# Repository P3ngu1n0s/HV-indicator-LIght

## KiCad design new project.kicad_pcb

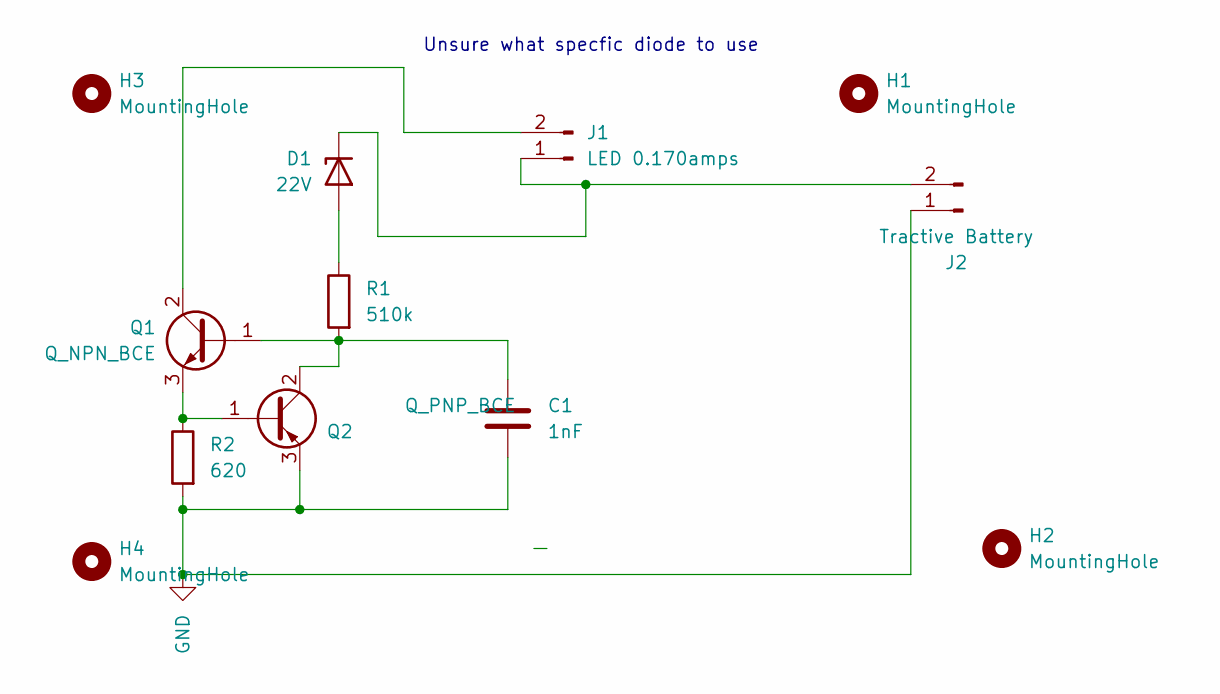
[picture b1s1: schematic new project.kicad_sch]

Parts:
C1: 1nF; C_0603_1608Metric
D1: 22V; D_DO-41_SOD81_P10.16mm_Horizontal
H1, H2, H3, H4: MountingHole; MountingHole_2.1mm
J1: LED 0.170amps; Molex_Micro-Fit_3.0_43650-0200_1x02_P3.00mm_Horizontal
J2: Tractive Battery; Molex_Micro-Fit_3.0_43650-0200_1x02_P3.00mm_Horizontal
Q1: Q_NPN_BCE; SOT-223-3_TabPin2
Q2: Q_PNP_BCE; SOT-223-3_TabPin2
R1: 510k; R_Axial_DIN0207_L6.3mm_D2.5mm_P10.16mm_Horizontal
R2: 620; R_Axial_DIN0207_L6.3mm_D2.5mm_P10.16mm_Horizontal

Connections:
GND: C1.2, J2.1, Q2.3 (E), R2.2
unnamed: D1.2 (A), R1.1
unnamed: D1.1 (K), J1.1, J2.2
unnamed: J1.2, Q1.2 (C)
unnamed: C1.1, Q1.1 (B), Q2.2 (C), R1.2
unnamed: Q1.3 (E), Q2.1 (B), R2.1

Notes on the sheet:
Unsure what specfic diode to use

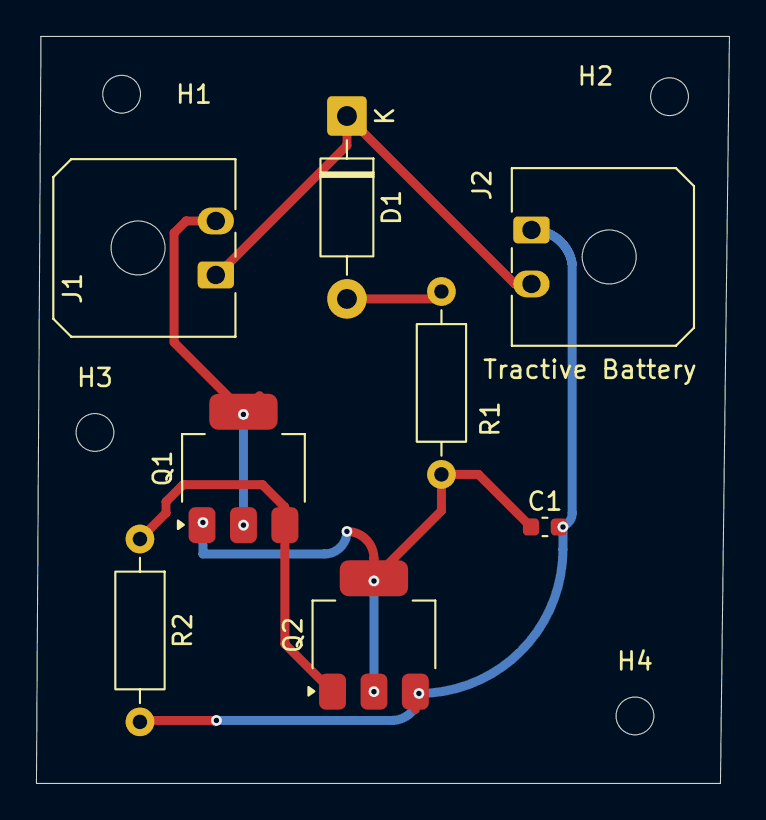
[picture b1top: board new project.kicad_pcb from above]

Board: 2 copper layers, 38.5 x 41.5 mm, 12 parts (0 on the bottom side), 6 nets.

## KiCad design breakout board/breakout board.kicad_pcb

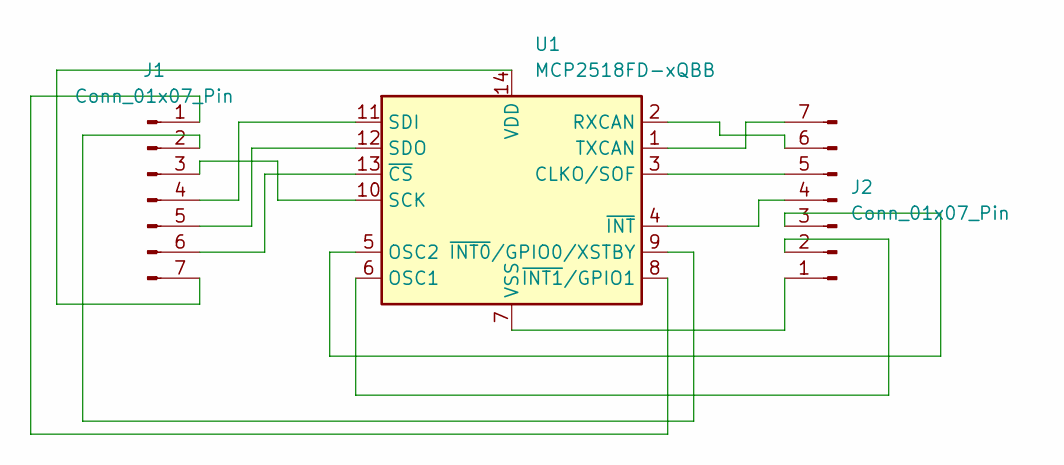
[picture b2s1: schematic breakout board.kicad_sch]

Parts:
J1, J2: Conn_01x07_Pin; PinHeader_1x07_P2.54mm_Vertical
U1: MCP2518FD-xQBB; DFN-14-1EP_3x4.5mm_P0.65mm_EP1.65x4.25mm

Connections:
unnamed: J1.1, U1.8 (~INT1/GPIO1)
unnamed: J1.2, U1.9 (~INT0/GPIO0/XSTBY)
unnamed: J1.3, U1.10 (SCK)
unnamed: J1.4, U1.11 (SDI)
unnamed: J1.5, U1.12 (SDO)
unnamed: J1.6, U1.13 (~CS)
unnamed: J1.7, U1.14 (VDD)
unnamed: J2.1, U1.7 (VSS), U1.15 (VSS)
unnamed: J2.2, U1.6 (OSC1)
unnamed: J2.3, U1.5 (OSC2)
unnamed: J2.4, U1.4 (~INT)
unnamed: J2.5, U1.3 (CLKO/SOF)
unnamed: J2.6, U1.2 (RXCAN)
unnamed: J2.7, U1.1 (TXCAN)

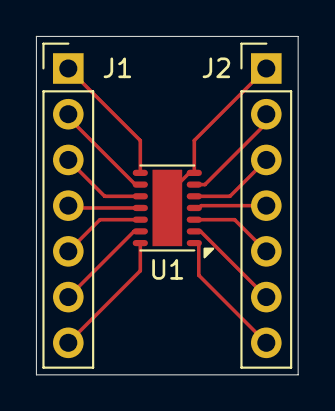
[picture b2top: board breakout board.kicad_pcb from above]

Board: 2 copper layers, 14.5 x 18.8 mm, 3 parts (0 on the bottom side), 14 nets.

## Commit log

2025-09-12 This is HV Inidcator for E25
2025-09-23 fixed
    fix
2025-09-23 sure
2025-09-23 Change
    NEW HV_INDICATOR folder
2025-09-23 something
2025-09-23 footprints added
2025-09-23 all footprints added and they ready for wriing
2025-09-23 Changed Resistor and LED footprint
2025-09-23 Wiring Done
2025-09-23 Autosave
2025-09-24 add everything
2025-09-24 everything works type
2025-09-24 Check
    Check
2025-09-25 Changed 1800 to 18000
    Resistor Value
2025-09-25 Updated HV
    Changed Resistor, Wiring and more.
2025-09-25 Push
2025-09-25 sure lets hope this fixes it
2025-09-26 UPDATE
    This should update everything now?? THINGS KEEP GETTING DELETED
2025-09-26 Update
    NOT LOADING IN GITHUB?
2025-09-26 Prototype
    Some error stills, but structure is overall built
2025-09-26 work
2025-09-26 Finally fixed
    Please upload the changes
2025-09-26 Check
    Redoing Wiring
2025-09-26 FInished
    Done
2025-09-26 Test
    Test
2025-09-26 Is it working
    Working
2025-09-26 where are you
2025-09-26 Small change
2025-09-26 Small bug check
    check
2025-10-01 Updated Schematic
    Based on new drawings
2025-10-01 Resistance Value Change
2025-10-03 Documentation
2025-10-15 G
    sdafasddfsaf
2025-10-16 finished HVIL
2025-10-16 type
